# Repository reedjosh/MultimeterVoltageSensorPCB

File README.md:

# MultimeterVoltageSensorPCB
Just install Kicad and open 'project1.pro'

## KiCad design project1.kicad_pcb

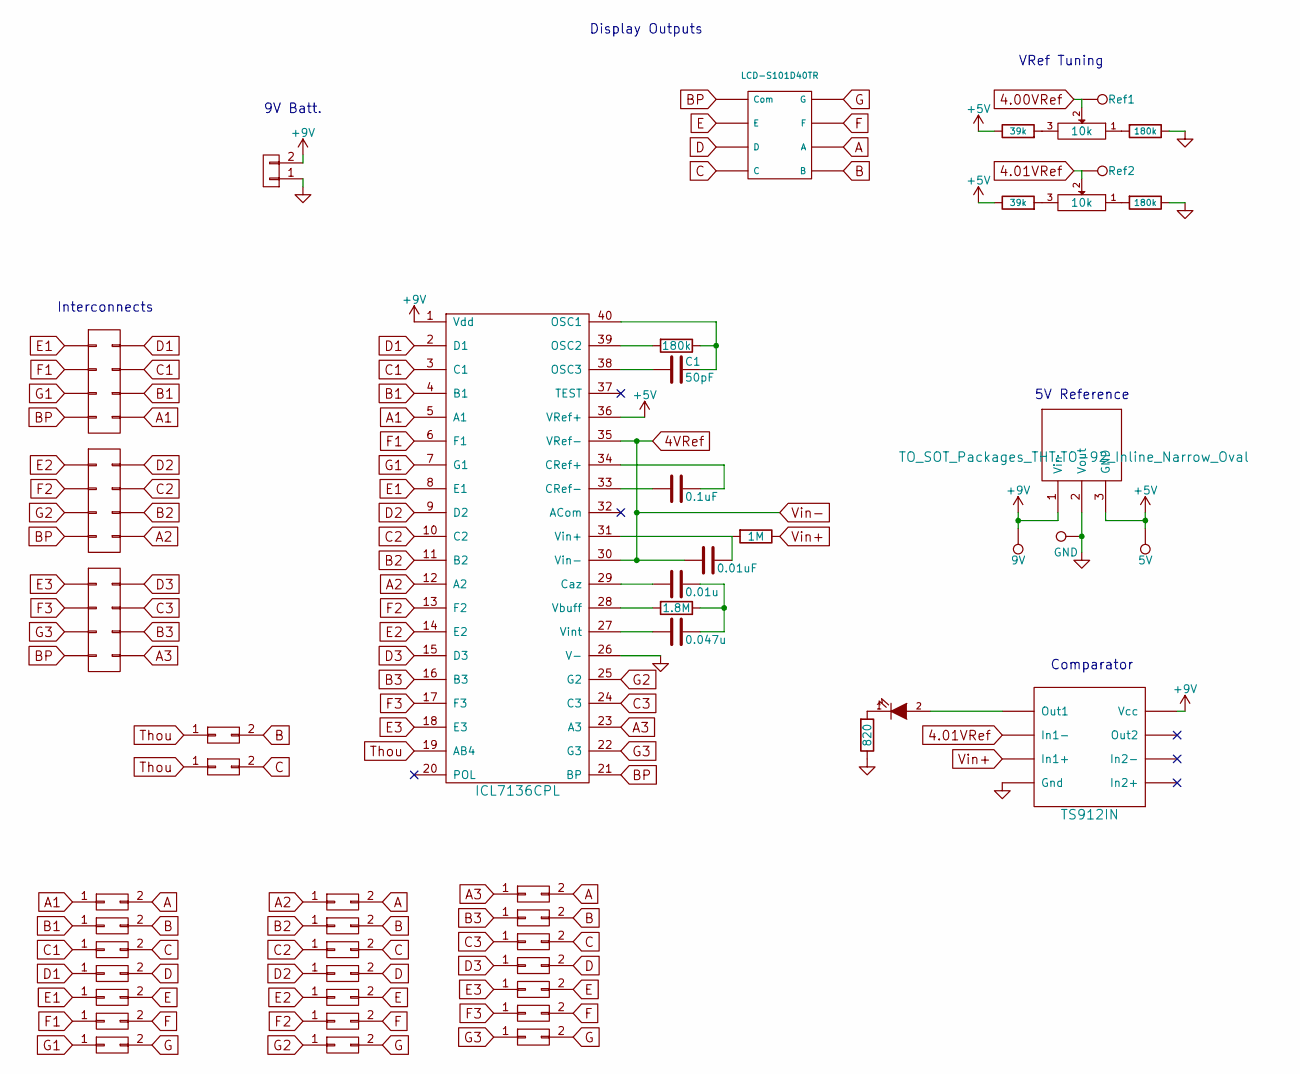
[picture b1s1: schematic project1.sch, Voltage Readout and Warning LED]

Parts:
C1: 50pF; C_Rect_L7_W2.5_P5
C2: 0.1uF; C_Rect_L7_W2.5_P5
C3: 0.01u; C_Rect_L7_W2.5_P5
C4: 0.047u; C_Rect_L7_W2.5_P5
C5: 0.01uF; C_Rect_L7_W2.5_P5
D1: LED; LED-3MM
I1: ICL7136CPL; DIP-40_W15.24mm
LCD1: LCD-S101D40TR
P1: CONN_01X02; Pin_Header_Straight_1x02
P3, P4, P6: CONN_02X04; IDC_Header_Straight_10pins
P7, P8, P9, P10, P11, P12, P13, P14, P15, P16, P17, P18, P19, P20, P21, P22, P23, P24, P25, P26, P27, P28, P29: CONN_02X01; Net_Tie_SMD
R1, R5, R7: 180k; Resistor_Horizontal_RM7mm
R2: 1.8M; Resistor_Horizontal_RM7mm
R3: 1M; Resistor_Horizontal_RM7mm
R4, R6: 39k; Resistor_Horizontal_RM7mm
R8: 820; Resistor_Horizontal_RM7mm
RV1, RV2: 10k; Potentiometer_Bourns_3296W_3-8Zoll_Inline_ScrewUp
U1: LT1460GIZ-5; TO-92_Inline_Narrow_Oval
U2: TS912IN; DIP-8_W7.62mm
W1: 9V; PINTST
W2: GND; PINTST
W3: 5V; PINTST
W4: Ref1; PINTST
W5: Ref2; PINTST

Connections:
4.00VRef: RV1.2, W4.1
4.01VRef: RV2.2, U2.2 (In1-), W5.1
4VRef: C5.2, I1.30 (Vin-), I1.35 (VRef-)
+5V: I1.36 (VRef+), R4.1, R6.1, U1.3 (GND), W3.1
+9V: I1.1 (Vdd), P1.2, U1.1 (Vin), U2.8 (Vcc), W1.1
A: LCD1.6 (A), P7.2, P15.2, P23.2
A1: I1.5 (A1), P6.8, P7.1
A2: I1.12 (A2), P3.8, P15.1
A3: I1.23 (A3), P4.8, P23.1
B: LCD1.5 (B), P8.2, P14.2, P16.2, P24.2
B1: I1.4 (B1), P6.6, P8.1
B2: I1.11 (B2), P3.6, P16.1
B3: I1.16 (B3), P4.6, P24.1
BP: I1.21 (BP), LCD1.1 (Com), P3.7, P4.7, P6.7
C: LCD1.4 (C), P9.2, P17.2, P22.2, P25.2
C1: I1.3 (C1), P6.4, P9.1
C2: I1.10 (C2), P3.4, P17.1
C3: I1.24 (C3), P4.4, P25.1
D: LCD1.3 (D), P10.2, P18.2, P26.2
D1: I1.2 (D1), P6.2, P10.1
D2: I1.9 (D2), P3.2, P18.1
D3: I1.15 (D3), P4.2, P26.1
E: LCD1.2 (E), P11.2, P19.2, P27.2
E1: I1.8 (E1), P6.1, P11.1
E2: I1.14 (E2), P3.1, P19.1
E3: I1.18 (E3), P4.1, P27.1
F: LCD1.7 (F), P12.2, P20.2, P28.2
F1: I1.6 (F1), P6.3, P12.1
F2: I1.13 (F2), P3.3, P20.1
F3: I1.17 (F3), P4.3, P28.1
G: LCD1.8 (G), P13.2, P21.2, P29.2
G1: I1.7 (G1), P6.5, P13.1
G2: I1.25 (G2), P3.5, P21.1
G3: I1.22 (G3), P4.5, P29.1
GND: I1.26 (V-), P1.1, R5.1, R7.1, R8.1, U1.2 (Vout), U2.4 (Gnd), W2.1
unnamed: C1.1, I1.40 (OSC1), R1.1
unnamed: C1.2, I1.38 (OSC3)
unnamed: C2.1, I1.34 (CRef+)
unnamed: C2.2, I1.33 (CRef-)
unnamed: C3.1, C4.1, R2.1
unnamed: C3.2, I1.29 (Caz)
unnamed: C4.2, I1.27 (Vint)
unnamed: C5.1, I1.31 (Vin+), R3.2
unnamed: D1.1 (K), R8.2
unnamed: D1.2 (A), U2.1 (Out1)
unnamed: I1.28 (Vbuff), R2.2
unnamed: I1.39 (OSC2), R1.2
unnamed: R4.2, RV1.3
unnamed: R5.2, RV1.1
unnamed: R6.2, RV2.3
unnamed: R7.2, RV2.1
Thou: I1.19 (AB4), P14.1, P22.1
Vin+: R3.1, U2.3 (In1+)

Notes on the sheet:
9V Batt.
5V Reference
Comparator
VRef Tuning
Display Outputs
Interconnects

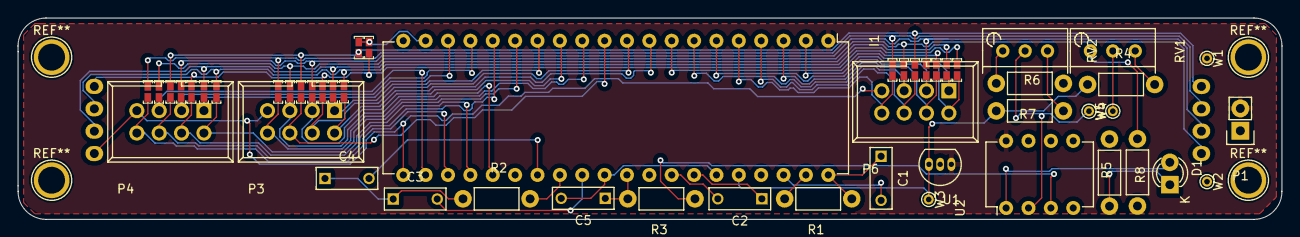
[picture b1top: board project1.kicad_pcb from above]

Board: 2 copper layers, 143.5 x 22.9 mm, 52 parts (0 on the bottom side), 53 nets.

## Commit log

2016-03-14 Updated Schematic Configuration; Needs Layout
2016-04-12 full redesign
2016-04-15 latest revision
